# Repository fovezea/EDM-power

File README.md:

# EDM Power Control System

A comprehensive ESP32-based EDM (Electrical Discharge Machining) power supply and control system with real-time web interface, PID control, and persistent settings management.

## 🎯 **Project Goals**

- **Real-time EDM Control**: Precise electrode positioning with PID feedback
- **Web Interface**: Modern responsive web UI for monitoring and control
- **Persistent Settings**: NVS-based settings storage with web configuration
- **Safety Features**: Limit switch protection and emergency stops
- **Modular Design**: Clean separation of concerns for maintainability

### **EDM Philosophy & Approach**

EDM machines, due to the spark (plasma) not being fully understood and the lack of a mathematical model that fits the way we try to simplify the equations, are still esoteric in nature and there is still a lot of empirical approach. Combined with the variety of materials and electrodes, this creates a complex situation.

As far as I understand, there is not a single type of power source in an industrial machine, but rather a combination of several sources depending on the operation. The target is to have flexibility to control the same hardware to do as much as possible.

There is a lot of documentation and publications out there, but there is still a gap between implementation and theoretical approach.

## ✨ **Current Features**

### 🔧 **Core EDM Functionality**
- **Stepper Motor Control**: Smooth acceleration/deceleration with RMT peripheral
- **PID Control Loop**: Configurable proportional, integral, and derivative gains
- **Gap Voltage Monitoring**: Real-time ADC sampling with configurable blanking delay
- **PWM Power Generation**: Half-bridge IGBT control with dead time protection
- **Safety Interlocks**: Limit switch protection and emergency stop functionality

### 🌐 **Web Interface & Connectivity**
- **WiFi Station Mode**: Automatic connection with retry logic
- **Real-time Web UI**: Modern responsive interface accessible via browser
- **WebSocket Communication**: Live status updates and command control
- **Cross-platform**: Works on desktop, tablet, and mobile devices

### ⚙️ **Settings Management**
- **Persistent Storage**: NVS-based settings that survive power cycles
- **Web Configuration**: Real-time parameter adjustment via web interface
- **Default Values**: Automatic fallback to sensible defaults
- **Settings Reset**: One-click restore to factory defaults

### 📊 **Configurable Parameters**
- **PWM Duty Cycle**: 1-99% with real-time adjustment
- **ADC Blanking Delay**: 10-200 ticks for noise filtering
- **PID Parameters**: 
  - Kp (Proportional): 0.000-1.000
  - Ki (Integral): 0.000-1.000  
  - Kd (Derivative): 0.000-1.000
  - Setpoint: 0-4095 ADC value
- **Speed Settings**: Jog and cut speeds in mm/s

## 🚀 **Getting Started**

### **Prerequisites**
- ESP-IDF v5.4.1 or later
- ESP32 development board
- DRV8825 stepper motor driver
- 4-wire stepper motor
- Half-bridge IGBT module
- Limit switch and control buttons

### **Hardware Connections**

```
+---------------------------+             +--------------------+      +--------------+
|          ESP32 Board      |             |       DRV8825      |      |    4-wire    |
|                       GND +-------------+ GND                |      |     Step     |
|                           |             |                    |      |     Motor    |
|                       3V3 +-------------+ VDD             A+ +------+ A+           |
|                           |             |                    |      |              |
|       GPIO 2 (DIR)        +------------>+ DIR             A- +------+ A-           |
|                           |             |                    |      |              |
|       GPIO 4 (STEP)       +------------>+ STEP            B- +------+ B-           |
|                           |             |                    |      |              |
|                           |      3V3----+ nSLEEP          B+ +------+ B+           |
|                           |             |                    |      +--------------+
|                           |      3V3----+ nRST            VM +-------------------+
|                           |             |                    |                   |
|                           |  3V3|GND----+ M2             GND +----------+        |
|                           |             |                    |          |        |
|                           |  3V3|GND----+ M1                 |          |        |
|                           |             |                    |          |        |
|                           |  3V3|GND----+ M0                 |      +---+--------+-----+
|                           |             |                    |      |  GND     +12V    |
|       GPIO 0 (ENABLE)     +------------>+ nEN                |      |   POWER SUPPLY   |
+---------------------------+             +--------------------+      +------------------+

PWM Outputs:
- GPIO 16 (PWM0A) -> IGBT High Side
- GPIO 17 (PWM0B) -> IGBT Low Side
- GPIO 18 (CAP)   -> External Signal Capture

Control Inputs:
- GPIO 12 (JOG_UP)     -> Jog Up Button
- GPIO 13 (JOG_DOWN)   -> Jog Down Button  
- GPIO 14 (LIMIT)      -> Limit Switch
- GPIO 15 (START_CUT)  -> Start/Stop Button

ADC Input:
- GPIO 6 (ADC_CH6)     -> Gap Voltage Sensing
```

### **Build and Flash**

1. **Configure WiFi** (optional):
   ```bash
   idf.py menuconfig
   # Navigate to: Component config -> WiFi Configuration
   # Set your WiFi credentials
   ```

2. **Build and flash**:
   ```bash
   idf.py build
   idf.py -p [PORT] flash monitor
   ```

3. **Access Web Interface**:
   - Connect to the ESP32's WiFi network (if in AP mode)
   - Or connect to your WiFi and note the IP address from serial output
   - Open browser and navigate to: `http://[ESP32_IP_ADDRESS]`

## 📁 **Project Structure**

```
main/
├── main.c                 # Core application logic and task management
├── MCPWM_task.c          # PWM generation and PID control loop
├── ADC.c                 # ADC sampling and gap voltage capture
├── stepper_motor_encoder.c # RMT-based stepper motor control
├── wifi_connect.c        # WiFi station mode with auto-reconnect
├── web_server.c          # HTTP server and WebSocket communication
├── settings.c            # NVS-based persistent settings management
├── web_server.h          # Web interface definitions
├── wifi_connect.h        # WiFi connection interface
└── settings.h            # Settings management interface
```

## 🎛️ **Web Interface Features**

### **Real-time Monitoring**
- **Gap Voltage**: Live ADC readings with voltage conversion
- **PWM Duty Cycle**: Current duty cycle percentage
- **System Status**: Cutting state, limit switch, WiFi connection
- **Motor Position**: Current step position and speeds
- **PID Parameters**: Current Kp, Ki, Kd, and setpoint values

### **Control Panel**
- **EDM Control**: Start/Stop cutting operations
- **Manual Jogging**: Up/Down movement with safety limits
- **Home Position**: Return to reference position
- **Settings Reset**: Restore factory defaults

### **Parameter Configuration**
- **Duty Cycle Slider**: 1-99% PWM control
- **ADC Blanking Delay**: 10-200 ticks for noise filtering
- **PID Tuning**: Real-time adjustment of control parameters
- **Setpoint Control**: Target ADC value for gap control

## 🔧 **Technical Details**

### **RMT-Based Stepper Control**
One RMT TX channel can use different encoders in sequence, which is useful to generate waveforms that have multiple stages.

To smoothly drive a stepper motor, there are three phases: **Acceleration**, **Uniform**, and **Deceleration**. The code implements two encoders so that the RMT channel can generate waveforms with different characteristics:

* `curve_encoder` encodes the **Acceleration** and **Deceleration** phases
* `uniform_encoder` encodes the **Uniform** phase

### **PID Control Loop**
The system uses a PID controller to maintain optimal gap voltage:
- **Proportional (Kp)**: Responds to current error
- **Integral (Ki)**: Eliminates steady-state error
- **Derivative (Kd)**: Reduces overshoot and oscillations
- **Setpoint**: Target ADC value for gap control

### **Control Logic & Safety Features**

The main control loop implements comprehensive safety and operational logic:

- **Jogging Control**: Manual movement only allowed if limit switch is ON (not triggered)
- **EDM Cutting**: Only runs if not jogging, limit switch is ON, and start button is ON
- **Safety Inhibition**: If limit switch is OFF, all movement is inhibited (including jogging and EDM control)
- **Range Validation**: All parameters validated before application
- **Fault Logging**: Comprehensive error reporting

The loop now fully supports the new safety and control logic with clear separation of jog and cut operations.

### **Safety Features**
- **Limit Switch Protection**: Inhibits all movement when triggered
- **Emergency Stop**: Immediate halt of all operations
- **Range Validation**: All parameters validated before application
- **Fault Logging**: Comprehensive error reporting

### **Performance Characteristics**
- **Update Rate**: 50Hz PID control loop
- **ADC Resolution**: 12-bit (0-4095)
- **PWM Frequency**: 20kHz with configurable duty cycle
- **Stepper Resolution**: 200 steps/revolution
- **WebSocket Latency**: <100ms for real-time control

## 🛠️ **Configuration**

### **WiFi Setup**
Edit `main/wifi_connect.c` to configure your WiFi credentials:
```c
#define WIFI_SSID "your_wifi_ssid"
#define WIFI_PASS "your_wifi_password"
```

### **GPIO Configuration**
Modify GPIO assignments in `main/main.c`:
```c
#define STEP_MOTOR_GPIO_EN       0
#define STEP_MOTOR_GPIO_DIR      2
#define STEP_MOTOR_GPIO_STEP     4
#define JOG_UP_GPIO   12
#define JOG_DOWN_GPIO 13
#define LIMIT_SWITCH_GPIO 14
#define START_CUT_GPIO    15
```

### **Default Settings**
Adjust default values in `main/settings.h`:
```c
#define DEFAULT_DUTY_PERCENT 40
#define DEFAULT_ADC_BLANKING_DELAY 1
#define DEFAULT_PID_KP 0.05f
#define DEFAULT_PID_KI 0.01f
#define DEFAULT_PID_KD 0.0f
#define DEFAULT_PID_SETPOINT 1500
```

## 📈 **Future Enhancements**

- **External ADC Support**: Higher precision voltage measurement
- **Multi-axis Control**: Support for X, Y, Z positioning
- **G-code Interpreter**: CNC-style programming interface
- **Data Logging**: Historical performance tracking
- **Advanced PID Tuning**: Auto-tuning algorithms
- **Material Database**: Pre-configured settings for different materials

## 🤝 **Contributing**

This project is actively developed for EDM applications. Contributions are welcome for:
- Hardware improvements
- Control algorithm enhancements
- Web interface features
- Documentation updates

## 📄 **License**

This project is open source. See LICENSE file for details.

## 📸 **Project Hardware Setup**

Below is a photo of the current hardware setup:

---

**Note**: This hardware schematic is writen in Kicad 9 but so far is just  power stage control without the reset of the generator. It will be added soon
**Note**: This system is designed for educational and experimental use. Always follow proper safety procedures when working with high-voltage EDM systems.

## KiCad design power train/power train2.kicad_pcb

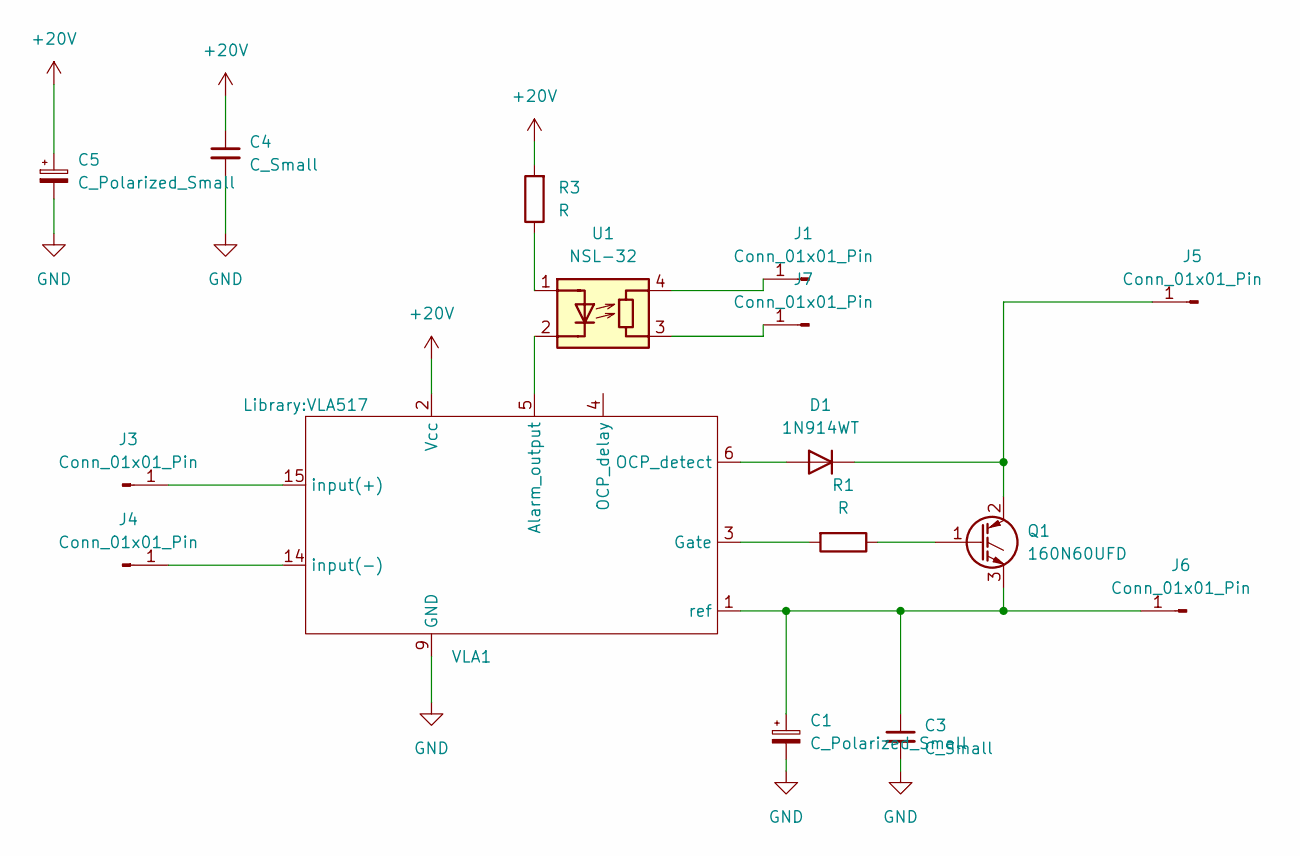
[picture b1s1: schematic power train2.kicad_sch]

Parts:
C1, C5: C_Polarized_Small; CP_Radial_D8.0mm_P3.50mm
C3, C4: C_Small; C_Axial_L5.1mm_D3.1mm_P7.50mm_Horizontal
D1: 1N914WT; D_SOD-523
J1, J3, J4, J5, J6, J7: Conn_01x01_Pin; TestPoint_THTPad_1.0x1.0mm_Drill0.5mm
Q1: 160N60UFD; TO-264-3_Vertical
R1, R3: R; R_Axial_DIN0309_L9.0mm_D3.2mm_P12.70mm_Horizontal
U1: NSL-32; Luna_NSL-32
VLA1: VLA517

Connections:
+20V: C4.1, C5.1, R3.2, VLA1.2 (Vcc)
GND: C1.2, C3.2, C4.2, C5.2, VLA1.9 (GND)
unnamed: D1.2 (A), VLA1.6 (OCP_detect)
unnamed: D1.1 (K), J5.1, Q1.2 (C)
unnamed: J1.1, U1.4 (R)
unnamed: J3.1, VLA1.15 (input(+))
unnamed: J4.1, VLA1.14 (input(-))
unnamed: C1.1, C3.1, J6.1, Q1.3 (E), VLA1.1 (ref)
unnamed: J7.1, U1.3 (R)
unnamed: Q1.1 (G), R1.1
unnamed: R3.1, U1.1 (A)
unnamed: U1.2 (K), VLA1.5 (Alarm_output)
unnamed: R1.2, VLA1.3 (Gate)

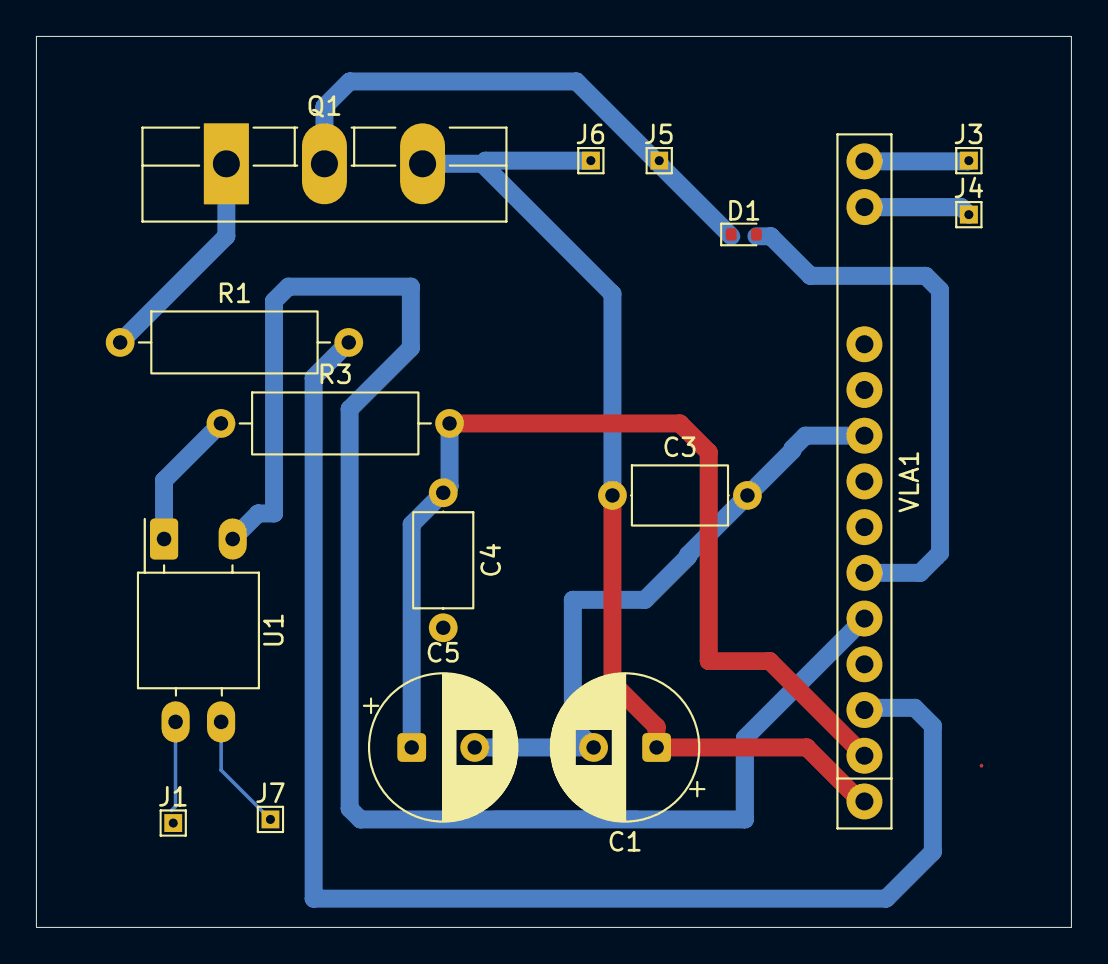
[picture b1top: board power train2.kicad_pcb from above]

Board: 2 copper layers, 57.5 x 49.5 mm, 16 parts (0 on the bottom side), 13 nets.

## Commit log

2025-06-09 proper ADC timing
2025-06-09 partial no crash
2025-06-10 stepper works
2025-06-10 ADC and Queue working
2025-06-10 Clean-up - all working
2025-06-19 change the ADC to latest
2025-06-19 ADC works well
2025-06-19 change from ledc to pcpwm
2025-06-20 added sparc on pin
2025-06-20 same
2025-06-23 control loop with ADC and spark on signal
2025-06-23 change tick rate on 1000hz
2025-06-23 nothing
2025-06-23 nu stiu
2025-06-23 not crushing
2025-06-23 nu mai crapa dar nu stiu daca merge
2025-06-24 code refactory
2025-06-24 added logic for buttons
2025-06-26 fixed ADC motor still crash
2025-06-26 added yeld for limit switch
2025-06-26 nu mai crapa are ADC on gpio16 on
2025-06-29 everithing seams to work
2025-06-29 hardware test stepper ok
2025-06-29 changed to s curve encoder
2025-06-30 corrected some bullshet from AI
2025-07-01 removed PWM-ledc
2025-07-01 readme
2025-07-01 calc freq from speed/mm
2025-07-01 Jog working better
2025-07-02 reademe update
2025-07-07 added schematic
2025-07-07 power train
2025-07-08 ADC adjust the duty cycle
2025-07-08 pin6 calback
2025-07-09 ping 6 callback working
2025-07-09 wi-fi and web server added
2025-07-09 added PID values to web
2025-07-09 updated redme.md
2025-07-09 web partialy working
2025-07-09 web interface is working better now and moust of t he button are functional now
2025-07-10 renamed some files
2025-07-10 impruved stepper task speed control to 2 miliseconds
